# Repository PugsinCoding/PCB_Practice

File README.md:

# PCB_Practice
Taking Circuits made by myself or in EE120B and turning them into PCBs

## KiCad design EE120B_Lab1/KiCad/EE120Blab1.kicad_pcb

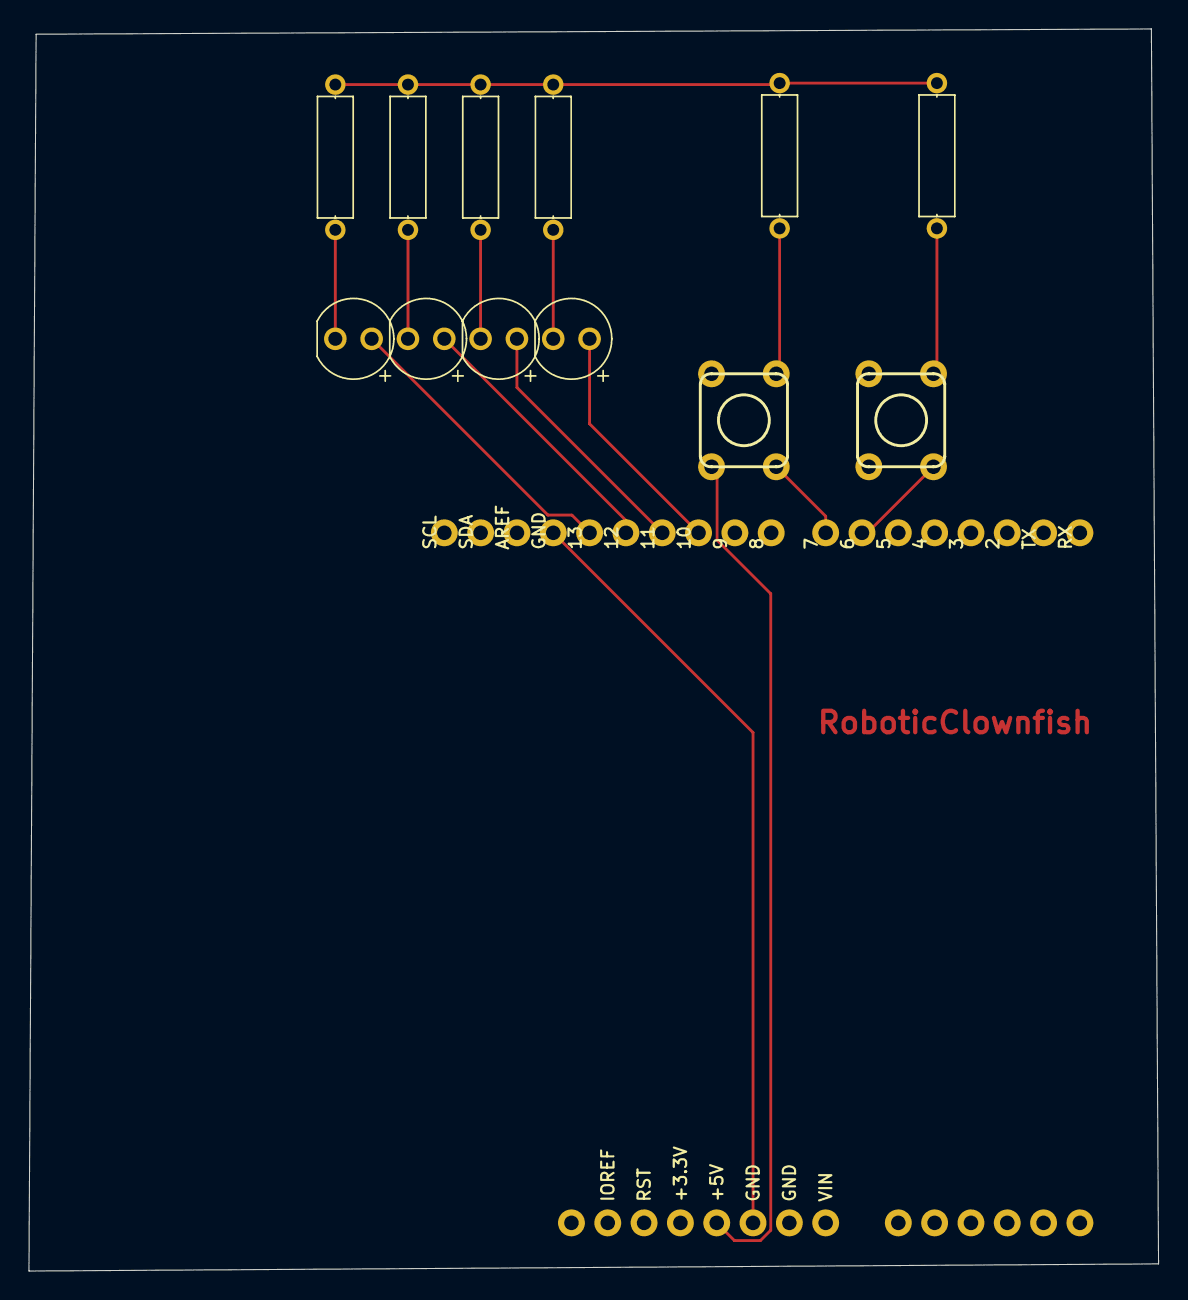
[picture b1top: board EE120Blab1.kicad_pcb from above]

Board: 2 copper layers, 79.0 x 86.9 mm, 13 parts (0 on the bottom side), 12 nets.

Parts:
D1, D2, D3, D4: LED_RED; LEDRD254W60D565H860B
R1, R2, R3, R4: 150; RESAD1016W63L850D250B
R5, R6: 1k; RESAD1016W63L850D250B
S1, S2: SWITCH_MOMENTARY; SWITCH-MOMENTARY-PTH-6.5MM
U1: ARDUINO-UNO-R3-SHIELD

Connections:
D1_C: D1.2, R1.1
D2_C: D2.2, R2.1
D3_C: D3.2, R3.1
D4_C: D4.2, R4.1
U1_5V: S1.1, S1.2, S2.1, S2.2, U1.5V
U1_D6: R6.1, S2.3, S2.4, U1.D6
U1_D7: R5.1, S1.3, S1.4, U1.D7
U1_D10: D4.1, U1.D10
U1_D11: D3.1, U1.D11
U1_D12: D2.1, U1.D12
U1_D13: D1.1, U1.D13
U1_GND: R1.2, R2.2, R3.2, R4.2, R5.2, R6.2, U1.GND@0, U1.GND@1, U1.GND@2
